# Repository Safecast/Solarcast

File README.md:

# Solarcast
Safecast Solarcast sensor device is designed to operate off-grid and sense environmental parameters. It consists of 5 key modules designed for maximal reuse.

## Modular design
 1. [Air sensor module](/air-module)
 2. [Geiger sensor module](/geiger-module)
 3. [Battery power module](/battery-module)
 4. [Communications module](/communications-module)
 5. [Gateway module](/gateway-module)

In an optimal design all modules have their own BLE processor and can be directly combined between each other, initial design is however only partially modular.

## Design parameters
The PCBs have to be designed in KiCad package.

---

#### License

Open data generated by Safecast is licensed under [CC0](https://creativecommons.org/publicdomain/zero/1.0/legalcode).

Hardware, Software, and Firmware licenses TBD.

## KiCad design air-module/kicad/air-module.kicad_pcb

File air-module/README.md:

# Air module for Solarcast
Air module is a standalone sensor unit that is a part of the Solarcast assembly and houses two particle sensors and a temperature and humidity sensor along with an optional BLE processor module.

## Design specification
* BLE module NRF [nRF52832 ANT](https://www.tindie.com/products/hnhoan/nrf52832-ant-bluetooth-le-arm-cortex-m4f-30-io/)
* Particle sensor [Alphasense OPC-N2](http://www.alphasense.com/index.php/products/optical-particle-counter/) (SPI)
* Particle sensor [PM2.5 PMS 5003](http://www.plantower.com/en/content/?108.html) (UART)
* Temperature and humidity sensor BME280 sensor (I2C SDO high 0x77)
* 5V power supply via USB connector (no USB data)
* Outdoor enclosure [PNR-2603](http://eu.mouser.com/ProductDetail/Bud-Industries/PNR-2603/?qs=sGAEpiMZZMsrGrAVj6eTvTO11XxqWC53gJbMy7TDIp4%3d)
* Dual channel high side Switch high-side switch [TPS2034D](http://www.ti.com/product/TPS2034D?keyMatch=TPS2034D&tisearch=Search-EN-Everything) each output for one AIR sensor, with bypass header jumpers.

## Extended details
* Waterproof [USB connector](http://eu.mouser.com/ProductDetail/Conxall-Switchcraft/DCP-USBCB-SC/?qs=sGAEpiMZZMulM8LPOQ%252byk0tOUVtDtVQ0KVOITCuLB%252bPJPE9H7T7ELA%3d%3d
) (data lines carry SWDIO & SWCLK signals)
* Internal 3V3 regulator
* Expansion connector 2x6 (IDC connector) with SPI, I2C and UART

## Connection details
The devices have the following connection details:

* Alphasense (leftmost wire on connector with wire crimp contacts facing up going away from you) Connector: Molex 'Pico Clasp' 6 way Housing, Part Number 501330-0600
 1. 5V
 2. SPI-SCLK
 3. SPI-MISO
 4. SPI-MOSI
 5. SPI-CS
 6. GND

* Plantower, no connector, solder wires
  1. 5V
  2. GND
  3. N/C
  4. RX (optional SCL) (add 0 ohm resistors to select between uart and i2c pins)
  5. TX (optional SDA) (add 0 ohm resistors to select between uart and i2c pins)
  6. N/C
  7. comm config (add solder jumpers for pull up/down)
  8. comm config (add solder jumpers for pull up/down)

*  nRF52832 module
 * Pin 3: P0.23	LED-RED
 * Pin 5: P0.25	TWI-SDA
 * Pin 6: P0.26 TWI-SCL
 * Pin 7: P0.27 UMUX-INH
 * Pin 18: 3.3V
 * Pin 19: GND
 * Pin 20: P0.07 TX
 * Pin 21: SWCLK/TCK
 * Pin 22: SWDIO/TMS
 * Pin 23: P0.08 RX
 * Pin 28: P0.03 SPI-MOSI
 * Pin 29: P0.04 SPI-MISO
 * Pin 30: P0.05 SPI-CS
 * Pin 31: P0.06 SPI-SCLK

 ## Board layout
 The PCB board has a connector of each particle sensor, BLE module on the short board edge and the USB connector on the edge between two rounded corners.

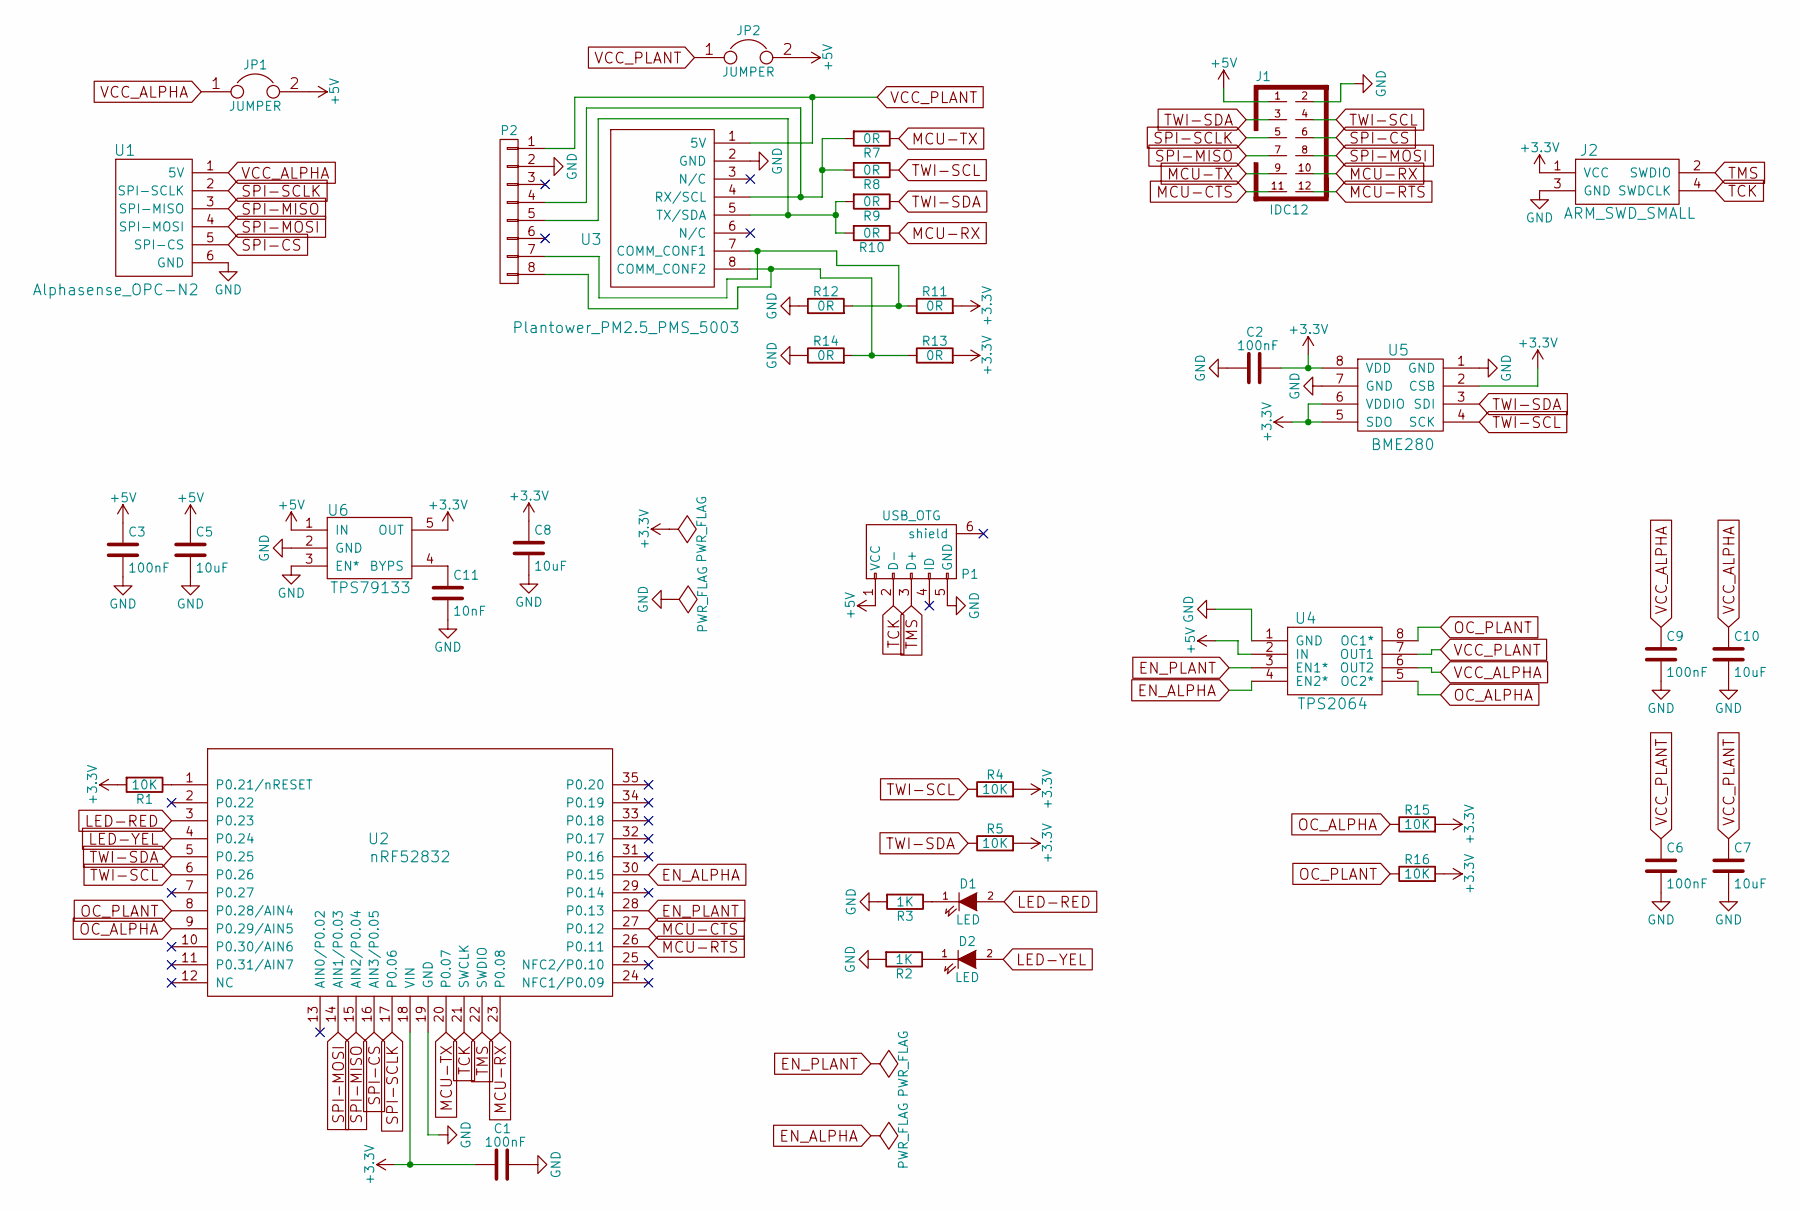
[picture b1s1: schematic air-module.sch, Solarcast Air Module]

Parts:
C1, C2, C3, C6, C9: 100nF; 0603_HandSoldering
C5, C7, C8, C10: 10uF; 0805_HandSoldering
C11: 10nF; 0603_HandSoldering
D1, D2: LED; LED_0603_HandSoldering
J1: IDC12; IDC12_connector
J2: ARM_SWD_SMALL; Socket_Strip_Straight_2x02
JP1, JP2: JUMPER; Socket_Strip_Straight_1x02
P1: USB_OTG; DCP-USBCB-SC
P2: CONN_01X08; Molex-53047-0810
R1, R4, R5, R15, R16: 10K; 0603_HandSoldering
R2, R3: 1K; 0603_HandSoldering
R7, R8, R9, R10, R11, R12, R13, R14: 0R; 0603_HandSoldering
U1: Alphasense_OPC-N2; Molex_501331-0607
U2: nRF52832; nRF52832-SMD
U3: Plantower_PM2.5_PMS_5003; Socket_Strip_Straight_1x08
U4: TPS2064
U5: BME280
U6: TPS79133

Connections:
+3V3: C1.2, C2.1, C8.1, J2.1 (VCC), R1.2, R4.2, R5.2, R11.2, R13.2, R15.2, R16.2, U2.18 (VIN), U5.2 (CSB), U5.5 (SDO), U5.6 (VDDIO), U5.8 (VDD), U6.5 (OUT)
+5V: C3.1, C5.1, J1.1, JP1.2, JP2.2, P1.1 (VCC), U4.2 (IN), U6.1 (IN)
EN_ALPHA: U2.30 (P0.15), U4.4 (EN2*)
EN_PLANT: U2.28 (P0.13), U4.3 (EN1*)
GND: C1.1, C2.2, C3.2, C5.2, C6.2, C7.2, C8.2, C9.2, C10.2, C11.2, J1.2, J2.3 (GND), P1.5 (GND), P2.2, R2.2, R3.2, R12.1, R14.1, U1.6 (GND), U2.19 (GND), U3.2 (GND), U4.1 (GND), U5.1 (GND), U5.7 (GND), U6.2 (GND), U6.3 (EN*)
LED-RED: D1.2 (A), U2.3 (P0.23)
LED-YEL: D2.2 (A), U2.4 (P0.24)
MCU-CTS: J1.11, U2.27 (P0.12)
MCU-RTS: J1.12, U2.26 (P0.11)
MCU-RX: J1.10, R10.1, U2.23 (P0.08)
MCU-TX: J1.9, R7.1, U2.20 (P0.07)
unnamed: C11.1, U6.4 (BYPS)
unnamed: D1.1 (K), R3.1
unnamed: D2.1 (K), R2.1
unnamed: P2.4, R7.2, R8.2, U3.4 (RX/SCL)
unnamed: P2.5, R9.2, R10.2, U3.5 (TX/SDA)
unnamed: P2.7, R11.1, R12.2, U3.7 (COMM_CONF1)
unnamed: P2.8, R13.1, R14.2, U3.8 (COMM_CONF2)
unnamed: R1.1, U2.1 (P0.21/nRESET)
OC_ALPHA: R15.1, U2.9 (P0.29/AIN5), U4.5 (OC2*)
OC_PLANT: R16.1, U2.8 (P0.28/AIN4), U4.8 (OC1*)
SPI-CS: J1.6, U1.5 (SPI-CS), U2.16 (AIN3/P0.05)
SPI-MISO: J1.7, U1.3 (SPI-MISO), U2.15 (AIN2/P0.04)
SPI-MOSI: J1.8, U1.4 (SPI-MOSI), U2.14 (AIN1/P0.03)
SPI-SCLK: J1.5, U1.2 (SPI-SCLK), U2.17 (P0.06)
TCK: J2.4 (SWDCLK), P1.2 (D-), U2.21 (SWCLK)
TMS: J2.2 (SWDIO), P1.3 (D+), U2.22 (SWDIO)
TWI-SCL: J1.4, R4.1, R8.1, U2.6 (P0.26), U5.4 (SCK)
TWI-SDA: J1.3, R5.1, R9.1, U2.5 (P0.25), U5.3 (SDI)
VCC_ALPHA: C9.1, C10.1, JP1.1, U1.1 (5V), U4.6 (OUT2)
VCC_PLANT: C6.1, C7.1, JP2.1, P2.1, U3.1 (5V), U4.7 (OUT1)

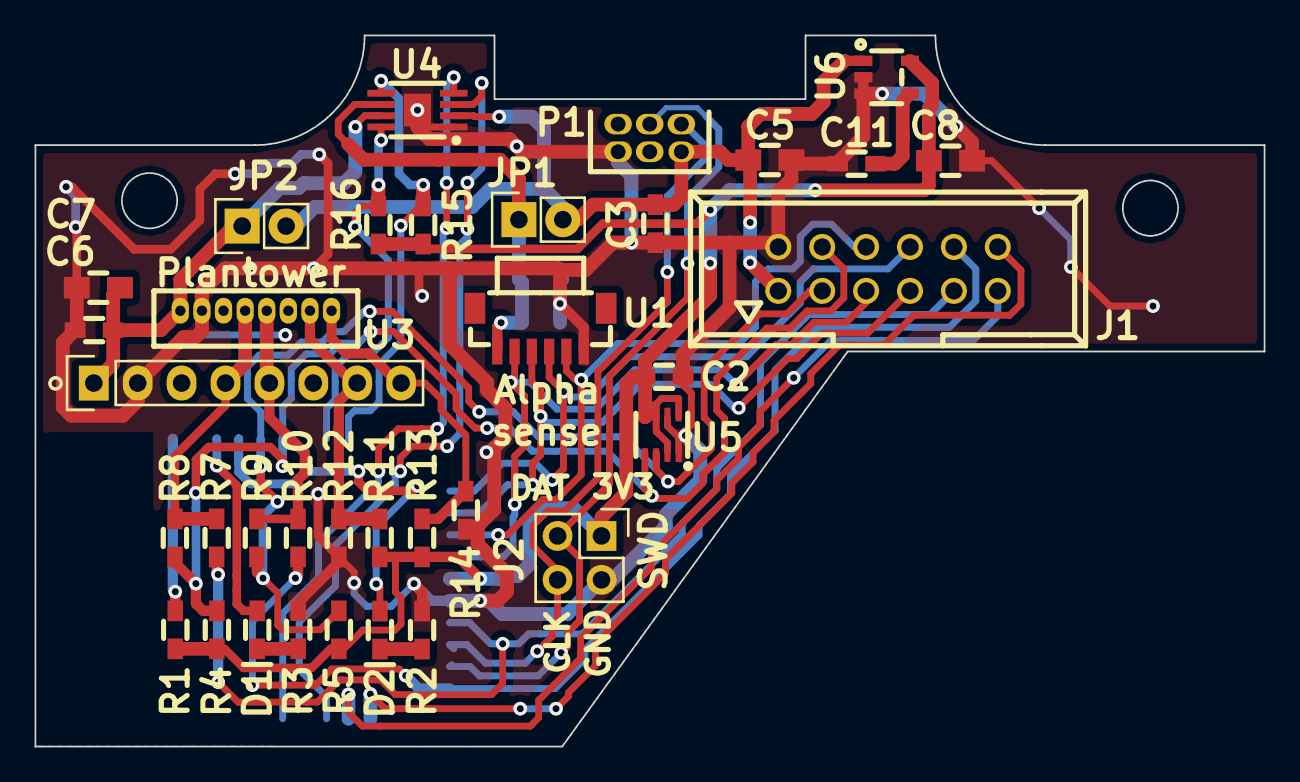
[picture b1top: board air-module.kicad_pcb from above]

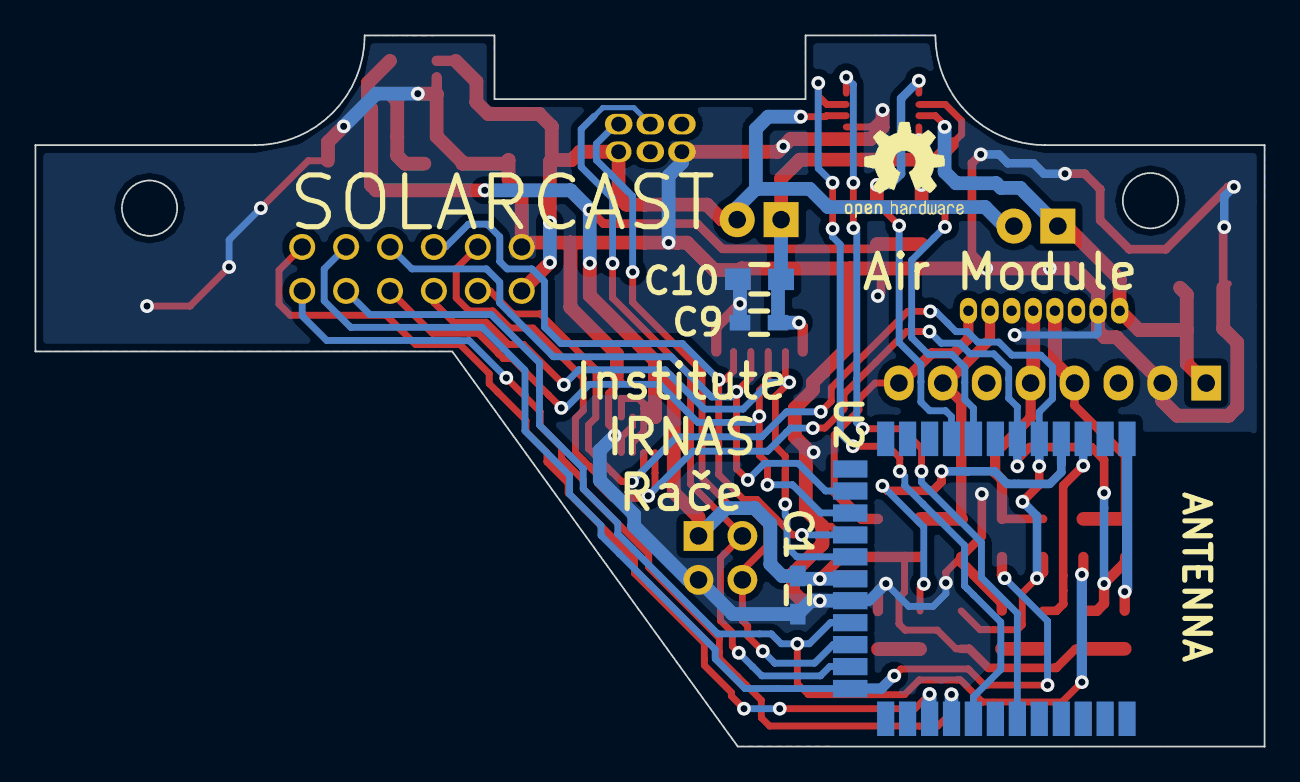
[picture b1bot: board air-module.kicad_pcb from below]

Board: 2 copper layers, 71.1 x 41.1 mm, 39 parts (4 on the bottom side), 31 nets.

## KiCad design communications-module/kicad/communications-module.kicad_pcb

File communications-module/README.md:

# Communications module for Solarcast
Communications module operates as the main module for the complete Solarcast assembly and is primarily a BLE device with other comms modules being plugged in.

## Design specification
* NRF module [nRF52832 ANT](https://www.tindie.com/products/hnhoan/nrf52832-ant-bluetooth-le-arm-cortex-m4f-30-io/)
* Programmer [CMSIS-DAP](https://www.tindie.com/products/hnhoan/cmsis-dap-arm-debug-jtagswd-module-drag-and-drop/)
* [GPS module](https://www.adafruit.com/products/790)
* [Adafruit FONA 3G module](https://www.adafruit.com/products/2691) (Note version difference between USA and EU)
* GSM antenna [FXUB66.07.0150C](http://www.mouser.com/ProductDetail/Taoglas/FXUB66070150C/?qs=L8NdhHdZHXxzH3hw8Na69A%3D%3D)
* LORA antenna [FXUB66.01.0150C](http://www.mouser.com/ProductDetail/Taoglas/FXUB66010150C/?qs=sGAEpiMZZMuBTKBKvsBmlEt2wojY8dgW39nSVW3ZfN0%3d)
* BME280 sensor (SDO low 0x76)
* Add accelerometer [LIS3DSH](https://www.adafruit.com/products/2809) footprint for the ic and pins for breakout
* UART MUX SN74LV4052AD SOIC-16
* USB connector to outside world http://eu.mouser.com/ProductDetail/Conxall-Switchcraft/DCP-USBCB-SC/?qs=sGAEpiMZZMulM8LPOQ%252byk0tOUVtDtVQ0KVOITCuLB%252bPJPE9H7T7ELA%3d%3d
* Case: PN-1335
* Add a GPIO expansion port for later work (UART for Air can be on it and I2C and SPI)
* Three internal USB connectors, not carrying USB data
 * USB0 - data pins select between I2C and programming pins
 * USB1 - data pins select between I2C and programming pins
 * USB2 - data pins select between GEIGER0/GEIGER1 and programming pins
* Connector for power module
* 2 groove expansion ports
* External power switch mounted on the box.

## Power supply configuration
Solar operation of the device and minimal power consumption in the standby state govern the design requirements.

Power flow: Solar cell-> Power module (built-in regulators) -> Comms module -> Power switch and fan out to:
* Switch high-side 5V - USB0 for Air module - ENABLE-AIR - 250mA peak - [TPS2034D](http://www.ti.com/product/TPS2034D?keyMatch=TPS2034D&tisearch=Search-EN-Everything) regulated from battery pack
* Switch high-side 5V - USB1 for Geiger module - ENABLE-GEIG - 50mA peak - [TPS2034D](http://www.ti.com/product/TPS2034D?keyMatch=TPS2034D&tisearch=Search-EN-Everything) regulated from battery pack
* Switch high-side 5V - USB2 -reserve- 1A peak [TPS2034D](http://www.ti.com/product/TPS2034D?keyMatch=TPS2034D&tisearch=Search-EN-Everything)
* Switch high-side 5V - backup - 1A peak [TPS2034D](http://www.ti.com/product/TPS2034D?keyMatch=TPS2034D&tisearch=Search-EN-Everything)

Power switch disconnects power between power module and comms module.

Add headers for mosfet bypass for current consumption measurement and jumpers prior to voltage regulators.

## Board layout
The board is designed as a main board with all other modules connecting to it.

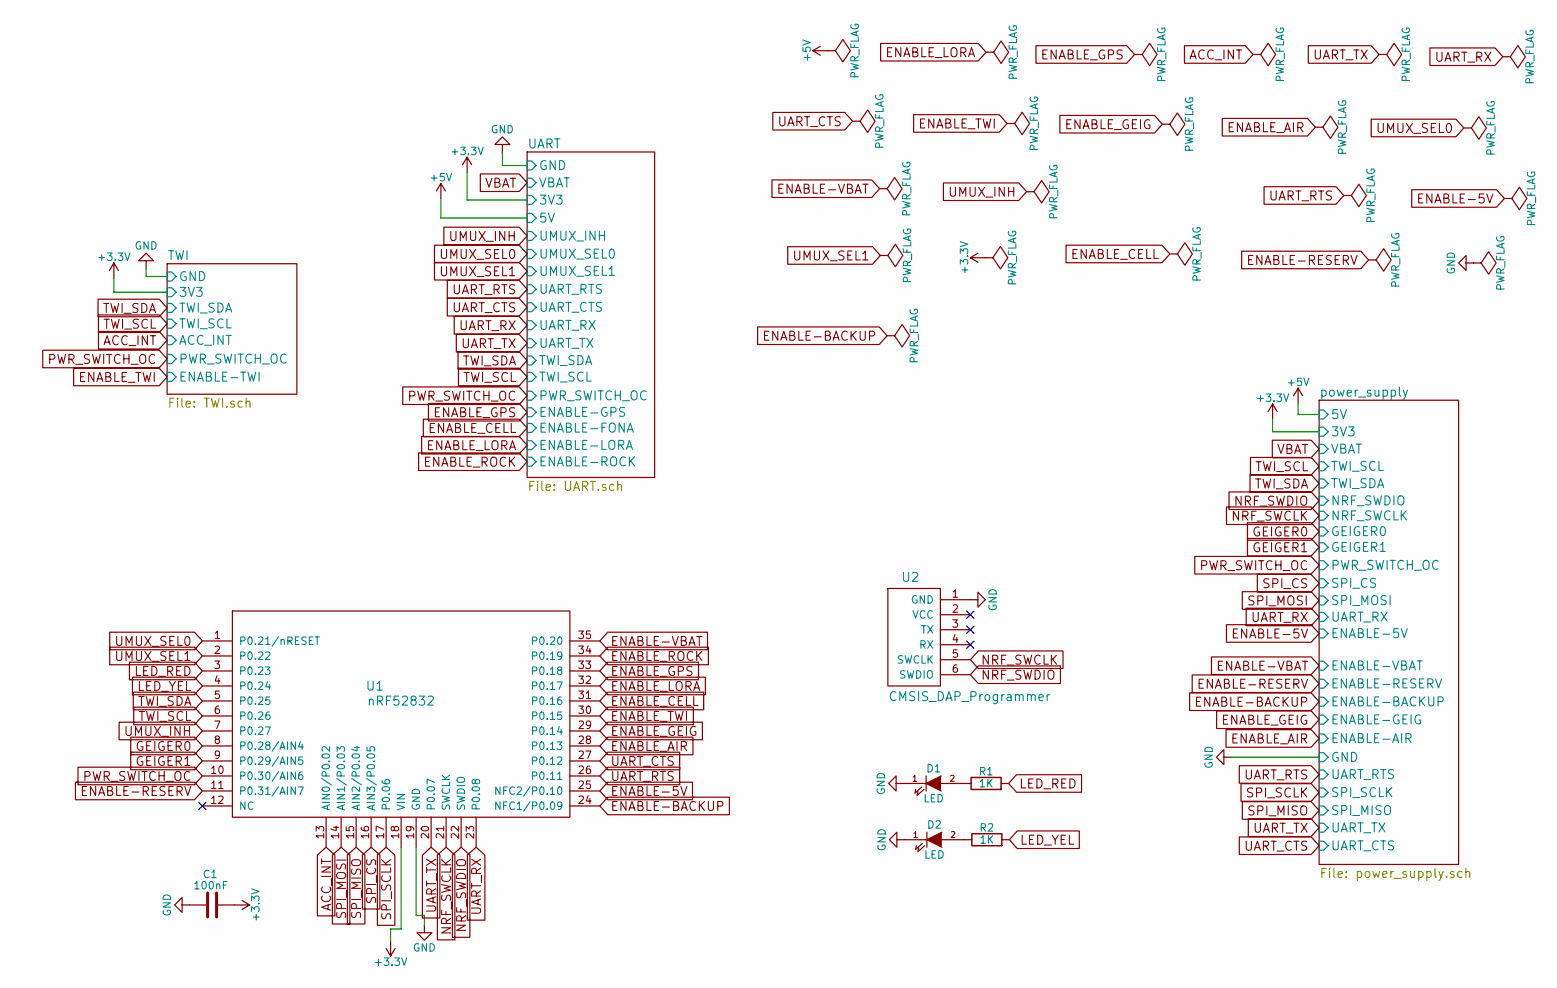
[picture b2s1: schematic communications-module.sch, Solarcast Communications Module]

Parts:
C1: 100nF; 0603_HandSoldering
D1, D2: LED; LED_0603_HandSoldering
R1, R2: 1K; 0603_HandSoldering
U1: nRF52832; nRF52832-SMD
U2: CMSIS_DAP_Programmer; CMSIS_DAP_Breakout

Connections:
+3V3: C1.2, U1.18 (VIN); also elsewhere on the board
ACC_INT: U1.13 (AIN0/P0.02); also elsewhere on the board
ENABLE-5V: U1.25 (NFC2/P0.10); also elsewhere on the board
ENABLE-AIR: U1.28 (P0.13); also elsewhere on the board
ENABLE-BACKUP: U1.24 (NFC1/P0.09); also elsewhere on the board
ENABLE-FONA: U1.31 (P0.16); also elsewhere on the board
ENABLE-GEIG: U1.29 (P0.14); also elsewhere on the board
ENABLE-GPS: U1.33 (P0.18); also elsewhere on the board
ENABLE-LORA: U1.32 (P0.17); also elsewhere on the board
ENABLE-RESERV: U1.11 (P0.31/AIN7); also elsewhere on the board
ENABLE-ROCK: U1.34 (P0.19); also elsewhere on the board
ENABLE-TWI: U1.30 (P0.15); also elsewhere on the board
ENABLE-VBAT: U1.35 (P0.20); also elsewhere on the board
GEIGER0: U1.8 (P0.28/AIN4); also elsewhere on the board
GEIGER1: U1.9 (P0.29/AIN5); also elsewhere on the board
LED_RED: R1.2, U1.3 (P0.23)
LED_YEL: R2.2, U1.4 (P0.24)
NRF_SWCLK: U1.21 (SWCLK), U2.5 (SWCLK); also elsewhere on the board
NRF_SWDIO: U1.22 (SWDIO), U2.6 (SWDIO); also elsewhere on the board
unnamed: D1.2 (A), R1.1
unnamed: D2.2 (A), R2.1
PWR_SWITCH_OC: U1.10 (P0.30/AIN6); also elsewhere on the board
SPI_CS: U1.16 (AIN3/P0.05); also elsewhere on the board
SPI_MISO: U1.15 (AIN2/P0.04); also elsewhere on the board
SPI_MOSI: U1.14 (AIN1/P0.03); also elsewhere on the board
SPI_SCLK: U1.17 (P0.06); also elsewhere on the board
TWI_SCL: U1.6 (P0.26); also elsewhere on the board
TWI_SDA: U1.5 (P0.25); also elsewhere on the board
UART_CTS: U1.27 (P0.12); also elsewhere on the board
UART_RTS: U1.26 (P0.11); also elsewhere on the board
UART_RX: U1.23 (P0.08); also elsewhere on the board
UART_TX: U1.20 (P0.07); also elsewhere on the board
UMUX_INH: U1.7 (P0.27); also elsewhere on the board
UMUX_SEL0: U1.1 (P0.21/nRESET); also elsewhere on the board

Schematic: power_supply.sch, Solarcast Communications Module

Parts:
J1: IDC12; IDC12_connector
JP1, JP2, JP5, JP6, JP7, JP8: JUMPER3; Socket_Strip_Straight_1x03_Pitch2.54mm
JP3, JP4, JP11, JP12: Jumper_NC_Small; Socket_Strip_Straight_1x02_Pitch2.54mm
P2, P3, P4: USB_A; USB_A_receptacle
P5: BACKUP; Socket_Strip_Straight_1x02_Pitch2.54mm
R3: 10K; 0603_HandSoldering
U3, U5: TPS2064
U4: PWR_CONN; IDC10_connector

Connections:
+3V3: R3.1, U4.5 (3V3); also elsewhere on the board
+5V: JP3.1, JP4.1, JP11.1, JP12.1, U3.2 (IN), U4.3 (5V), U5.2 (IN); also elsewhere on the board
AIR_5V: J1.1, JP11.2, P3.1 (VCC), U5.6 (OUT2)
BACKUP_5V: JP4.2, P5.1, U3.6 (OUT2)
ENABLE-5V: U4.4 (EN_5V); also elsewhere on the board
ENABLE-AIR: U5.4 (EN2*); also elsewhere on the board
ENABLE-BACKUP: U3.4 (EN2*); also elsewhere on the board
ENABLE-GEIG: U5.3 (EN1*); also elsewhere on the board
ENABLE-RESERV: U3.3 (EN1*); also elsewhere on the board
ENABLE-VBAT: U4.8 (EN_VBAT); also elsewhere on the board
GEIGER0: JP1.1; also elsewhere on the board
GEIGER1: JP2.3; also elsewhere on the board
GEIGER_5V: JP12.2, P2.1 (VCC), U5.7 (OUT1)
NRF_SWCLK: JP1.3, JP5.3, JP7.3; also elsewhere on the board
NRF_SWDIO: JP2.1, JP6.1, JP8.1; also elsewhere on the board
unnamed: JP1.2, P2.2 (D-)
unnamed: JP2.2, P2.3 (D+)
unnamed: JP5.2, P3.2 (D-)
unnamed: JP6.2, P3.3 (D+)
unnamed: JP7.2, P4.2 (D-)
unnamed: JP8.2, P4.3 (D+)
PWR_SWITCH_OC: R3.2, U3.5 (OC2*), U3.8 (OC1*), U5.5 (OC2*), U5.8 (OC1*); also elsewhere on the board
RESERV_5V: JP3.2, P4.1 (VCC), U3.7 (OUT1)
SPI_CS: J1.6; also elsewhere on the board
SPI_MISO: J1.7; also elsewhere on the board
SPI_MOSI: J1.8; also elsewhere on the board
SPI_SCLK: J1.5; also elsewhere on the board
TWI_SCL: J1.4, JP5.1, JP7.1, U4.1 (I2C_SCL); also elsewhere on the board
TWI_SDA: J1.3, JP6.3, JP8.3, U4.2 (I2C_SDA); also elsewhere on the board
UART_CTS: J1.11; also elsewhere on the board
UART_RTS: J1.12; also elsewhere on the board
UART_RX: J1.10; also elsewhere on the board
UART_TX: J1.9; also elsewhere on the board
VBAT: U4.7 (VBAT); also elsewhere on the board

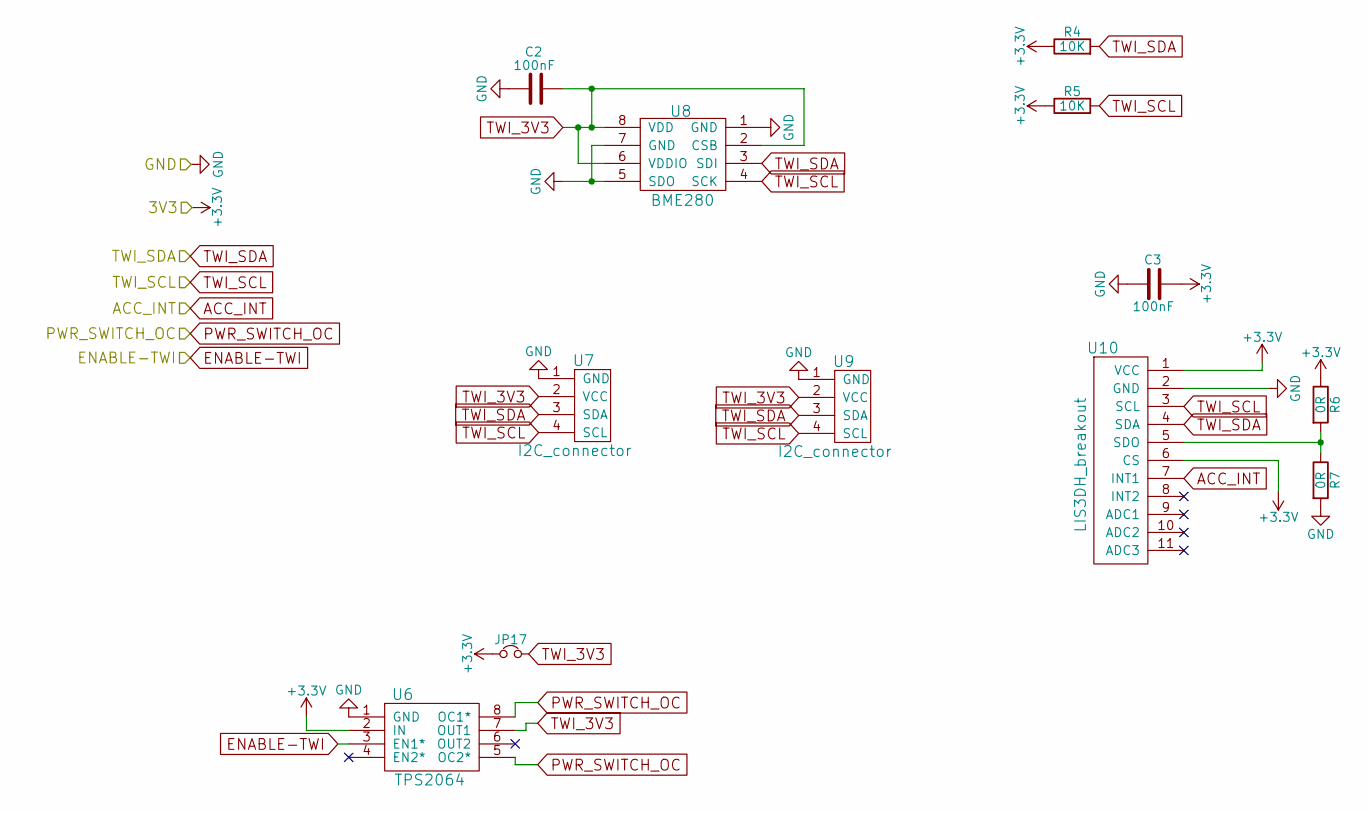
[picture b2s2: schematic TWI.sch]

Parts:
C2, C3: 100nF; 0603_HandSoldering
JP17: Jumper_NC_Small; Socket_Strip_Straight_1x02_Pitch2.54mm
R4, R5: 10K; 0603_HandSoldering
R6, R7: 0R; 0603_HandSoldering
U6: TPS2064
U7, U9: I2C_connector; DIP_Grove_4P-2_0
U8: BME280
U10: LIS3DH_breakout; LIS3DH_breakout_vertical

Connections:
+3V3: C3.2, JP17.1, R4.1, R5.1, R6.1, U6.2 (IN), U10.1 (VCC), U10.6 (CS); also elsewhere on the board
ACC_INT: U10.7 (INT1); also elsewhere on the board
ENABLE-TWI: U6.3 (EN1*); also elsewhere on the board
unnamed: R6.2, R7.1, U10.5 (SDO)
PWR_SWITCH_OC: U6.5 (OC2*), U6.8 (OC1*); also elsewhere on the board
TWI_3V3: C2.2, JP17.2, U6.7 (OUT1), U7.2 (VCC), U8.2 (CSB), U8.6 (VDDIO), U8.8 (VDD), U9.2 (VCC)
TWI_SCL: R5.2, U7.4 (SCL), U8.4 (SCK), U9.4 (SCL), U10.3 (SCL); also elsewhere on the board
TWI_SDA: R4.2, U7.3 (SDA), U8.3 (SDI), U9.3 (SDA), U10.4 (SDA); also elsewhere on the board

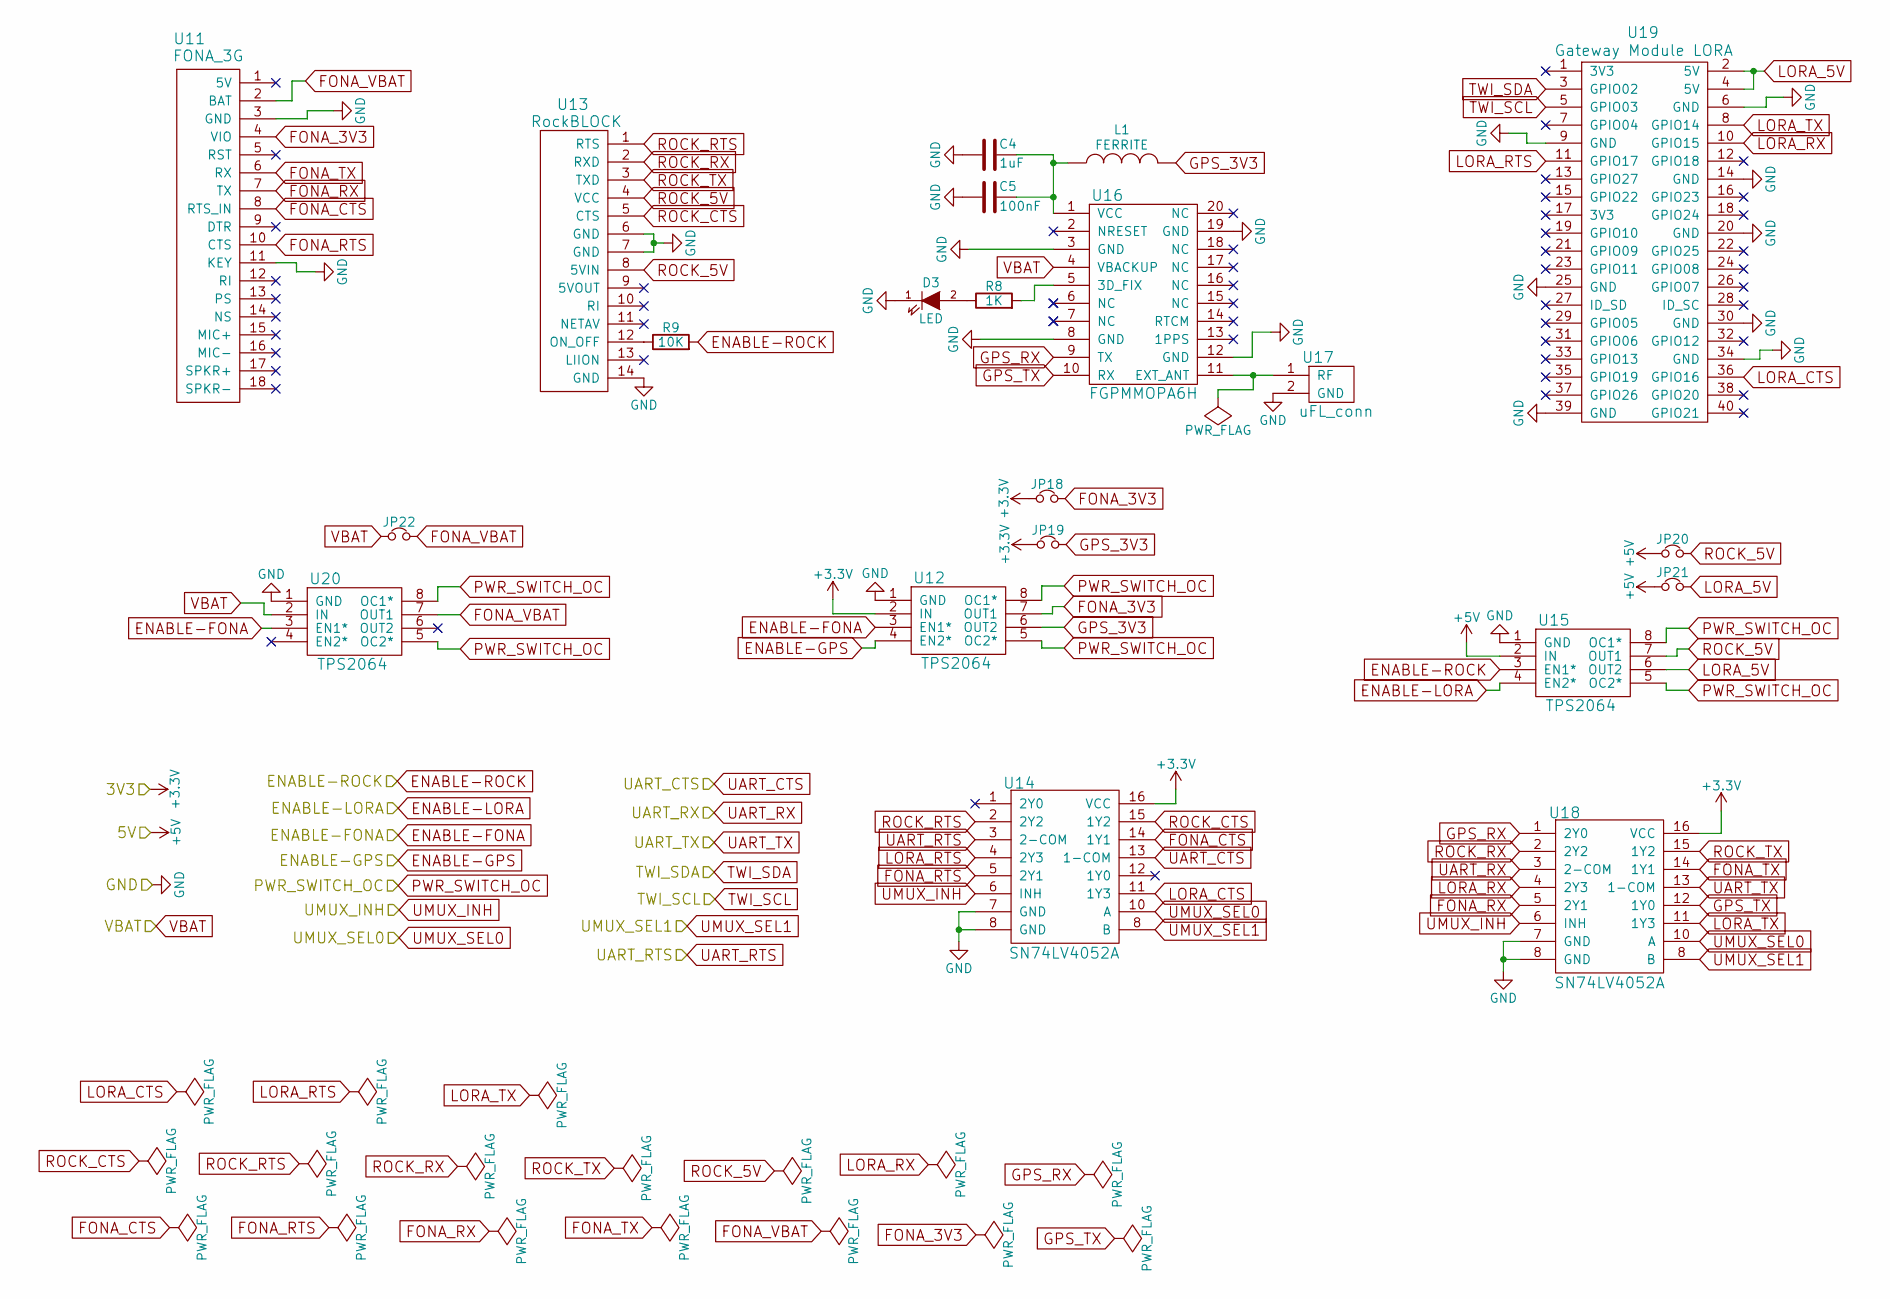
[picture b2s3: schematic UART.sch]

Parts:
C4: 1uF; 0603_HandSoldering
C5: 100nF; 0603_HandSoldering
D3: LED; LED_0603_HandSoldering
JP18, JP19, JP20, JP21, JP22: Jumper_NC_Small; Socket_Strip_Straight_1x02_Pitch2.54mm
L1: FERRITE; 0603_HandSoldering
R8: 1K; 0603_HandSoldering
R9: 10K; 0603_HandSoldering
U11: FONA_3G; FONA_3G_vertical
U12, U15, U20: TPS2064
U13: RockBLOCK; RockBlock_vertical
U14, U18: SN74LV4052A
U16: FGPMMOPA6H; FGPMMOPA6H_GPS
U17: uFL_conn; U.FL-R-SMT
U19: Gateway Module LORA; Solarcast_Gateway_Module

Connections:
+3V3: JP18.1, JP19.1, U12.2 (IN), U14.16 (VCC), U18.16 (VCC); also elsewhere on the board
+5V: JP20.1, JP21.1, U15.2 (IN); also elsewhere on the board
ENABLE-FONA: U12.3 (EN1*), U20.3 (EN1*); also elsewhere on the board
ENABLE-GPS: U12.4 (EN2*); also elsewhere on the board
ENABLE-LORA: U15.4 (EN2*); also elsewhere on the board
ENABLE-ROCK: R9.2, U15.3 (EN1*); also elsewhere on the board
FONA_3V3: JP18.2, U11.4 (VIO), U12.7 (OUT1)
FONA_CTS: U11.8 (RTS_IN), U14.14 (1Y1)
FONA_RTS: U11.10 (CTS), U14.5 (2Y1)
FONA_RX: U11.7 (TX), U18.5 (2Y1)
FONA_TX: U11.6 (RX), U18.14 (1Y1)
FONA_VBAT: JP22.2, U11.2 (BAT), U20.7 (OUT1)
GPS_3V3: JP19.2, L1.2, U12.6 (OUT2)
GPS_RX: U16.9 (TX), U18.1 (2Y0)
GPS_TX: U16.10 (RX), U18.12 (1Y0)
LORA_5V: JP21.2, U15.6 (OUT2), U19.2 (5V), U19.4 (5V)
LORA_CTS: U14.11 (1Y3), U19.36 (GPIO16)
LORA_RTS: U14.4 (2Y3), U19.11 (GPIO17)
LORA_RX: U18.4 (2Y3), U19.10 (GPIO15)
LORA_TX: U18.11 (1Y3), U19.8 (GPIO14)
unnamed: C4.2, C5.2, L1.1, U16.1 (VCC)
unnamed: D3.2 (A), R8.1
unnamed: R8.2, U16.5 (3D_FIX)
unnamed: R9.1, U13.12 (ON_OFF)
unnamed: U16.11 (EXT_ANT), U17.1 (RF)
PWR_SWITCH_OC: U12.5 (OC2*), U12.8 (OC1*), U15.5 (OC2*), U15.8 (OC1*), U20.5 (OC2*), U20.8 (OC1*); also elsewhere on the board
ROCK_5V: JP20.2, U13.4 (VCC), U13.8 (5VIN), U15.7 (OUT1)
ROCK_CTS: U13.5 (CTS), U14.15 (1Y2)
ROCK_RTS: U13.1 (RTS), U14.2 (2Y2)
ROCK_RX: U13.2 (RXD), U18.2 (2Y2)
ROCK_TX: U13.3 (TXD), U18.15 (1Y2)
TWI_SCL: U19.5 (GPIO03); also elsewhere on the board
TWI_SDA: U19.3 (GPIO02); also elsewhere on the board
UART_CTS: U14.13 (1-COM); also elsewhere on the board
UART_RTS: U14.3 (2-COM); also elsewhere on the board
UART_RX: U18.3 (2-COM); also elsewhere on the board
UART_TX: U18.13 (1-COM); also elsewhere on the board
UMUX_INH: U14.6 (INH), U18.6 (INH); also elsewhere on the board
UMUX_SEL0: U14.10 (A), U18.10 (A); also elsewhere on the board
VBAT: JP22.1, U16.4 (VBACKUP), U20.2 (IN); also elsewhere on the board

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
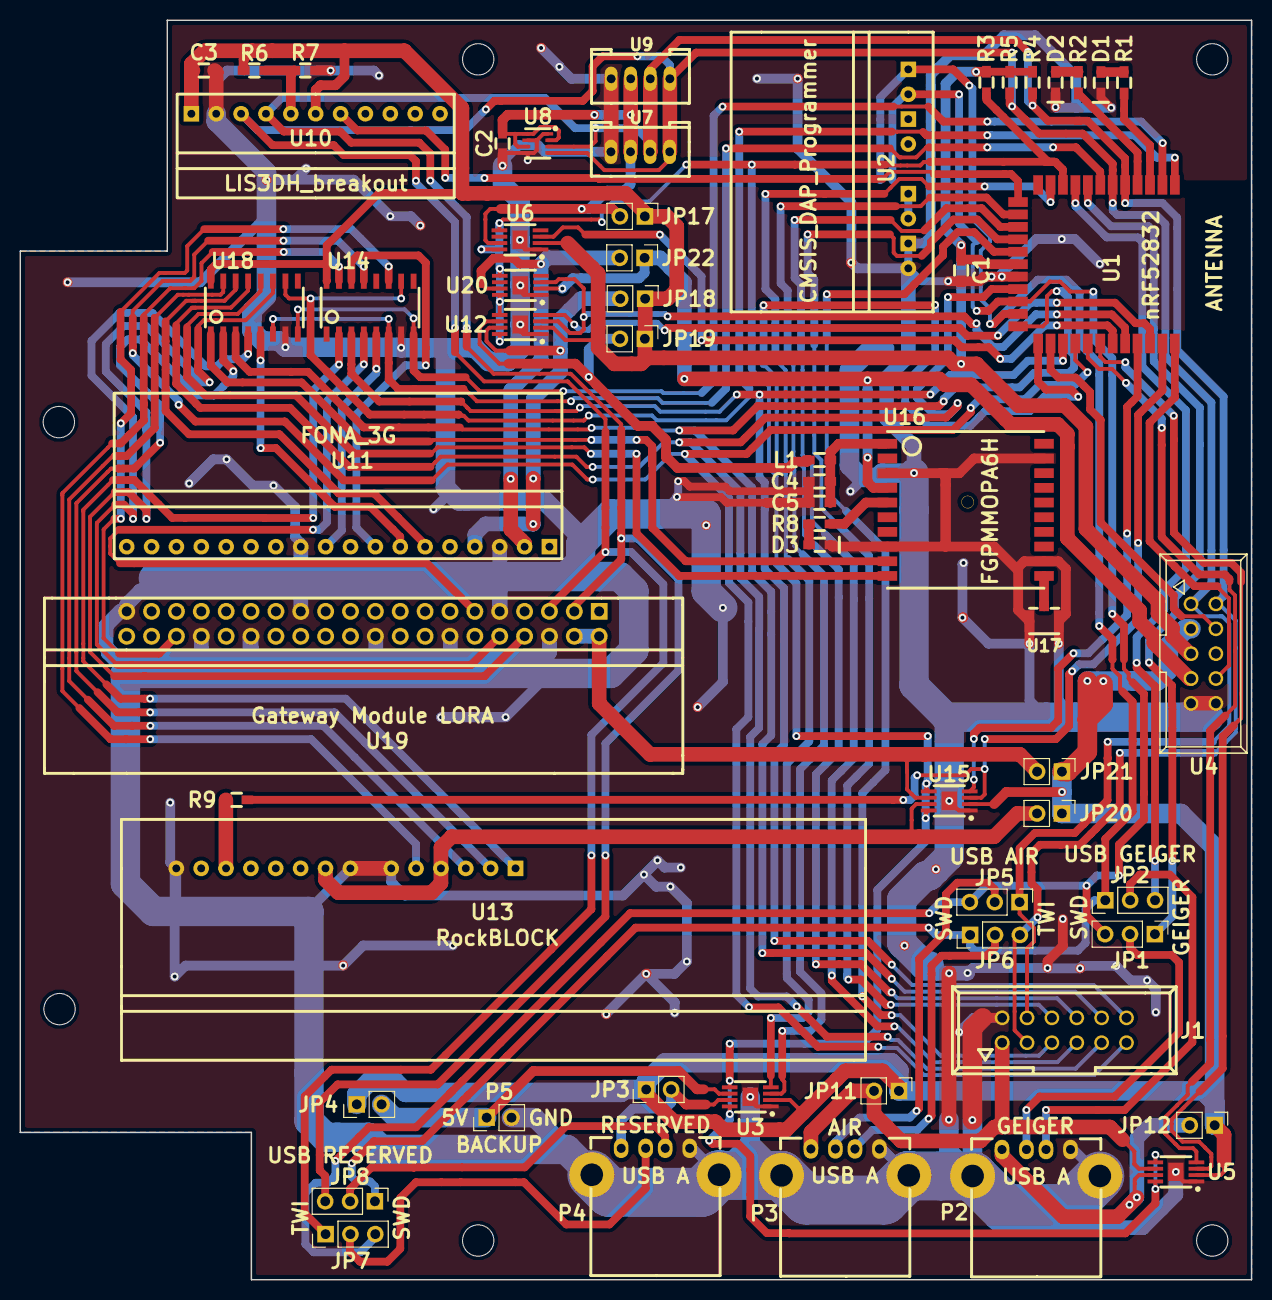
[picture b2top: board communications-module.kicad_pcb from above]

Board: 2 copper layers, 125.8 x 128.6 mm, 59 parts (0 on the bottom side), 74 nets.

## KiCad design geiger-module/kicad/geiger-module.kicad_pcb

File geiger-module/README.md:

# Geiger module for Solarcast
Geiger module is a standalone sensor unit that is a part of the Solarcast assembly and houses two Geiger tubes and a temperature and humidity sensor along with an optional BLE processor module.

## Design specification
* BLE module NRF [nRF52832 ANT](https://www.tindie.com/products/hnhoan/nrf52832-ant-bluetooth-le-arm-cortex-m4f-30-io/)
* Geiger pancake sensor (may be a stack of two)
* Geiger gamma compensated tube sensor
* Temperature and humidity sensor BME280 sensor (I2C SDO high 0x77)
* 5V power supply via USB connector (no USB data)
* Outdoor enclosure [PNR-2603](http://eu.mouser.com/ProductDetail/Bud-Industries/PNR-2603/?qs=sGAEpiMZZMsrGrAVj6eTvTO11XxqWC53gJbMy7TDIp4%3d)
* BLE module LED-RED

## Extended details
* Waterproof [USB connector](http://eu.mouser.com/ProductDetail/Conxall-Switchcraft/DCP-USBCB-SC/?qs=sGAEpiMZZMulM8LPOQ%252byk0tOUVtDtVQ0KVOITCuLB%252bPJPE9H7T7ELA%3d%3d
) (data lines carry SWDIO & SWCLK signals or Geiger 1 and Geiger 2 output signals, configuration depending via jumper)
* Internal 3V3 regulator
* 2pcs iRover HV board, stacked

## Connection details
The devices have the following connection details:

*  nRF52832 module
 * Pin 3: P0.23	LED-RED
 * Pin 5: P0.25	TWI-SDA
 * Pin 6: P0.26 TWI-SCL
 * Pin 7: P0.28	GEIGER0
 * Pin 8: P0.29 GEIGER1
 * Pin 18: 3.3V
 * Pin 19: GND
 * Pin 21: SWCLK/TCK
 * Pin 22: SWDIO/TMS

## Board layout
The PCB board has the two tubes mounted on one side with cables passing though and being connected directly to iRover boards on the other side. These boards are placed one next to the other. BLE module is placed somewhere along the edge, USB connector is on the short edge opposite to the side where the cutout for cables is.

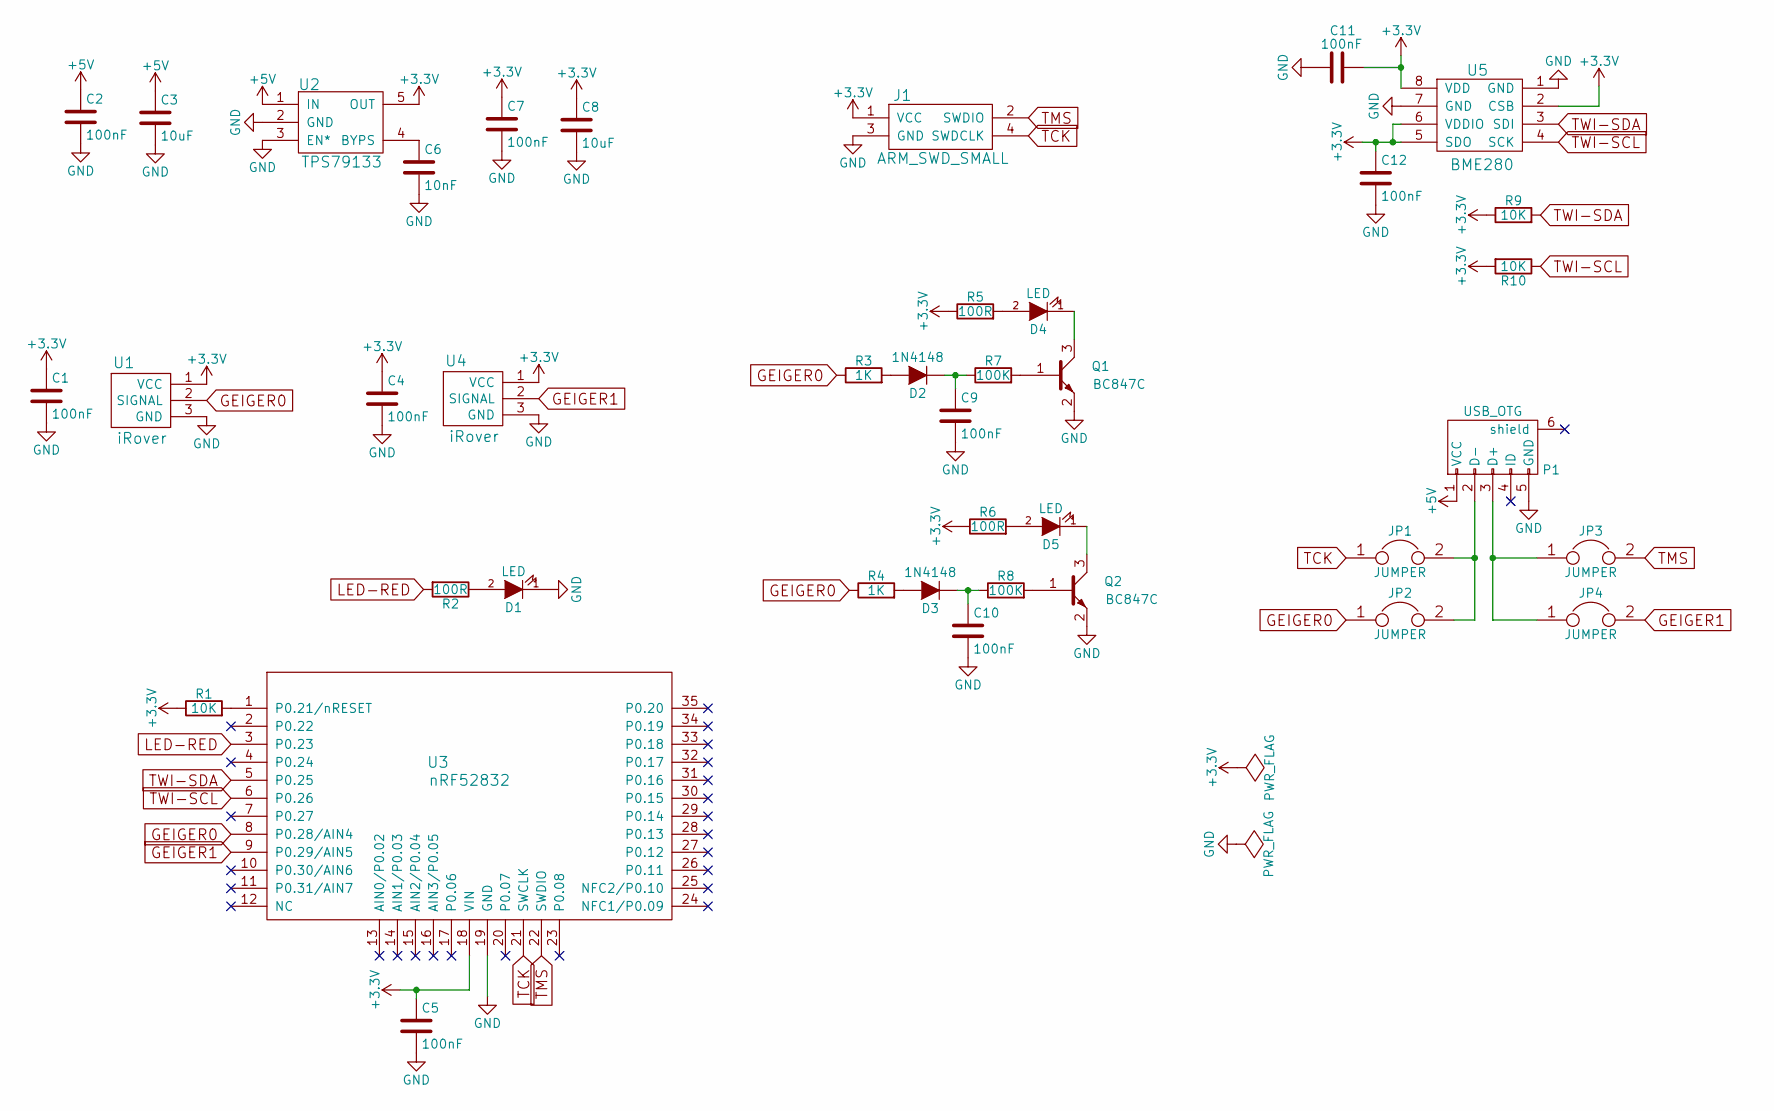
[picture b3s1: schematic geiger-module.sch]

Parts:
C1, C2, C4, C5, C7, C9, C10, C11, C12: 100nF; 0603_HandSoldering
C3, C8: 10uF; 0603_HandSoldering
C6: 10nF; 0603_HandSoldering
D1, D4, D5: LED; LED_0603_HandSoldering
D2, D3: 1N4148; SOD-323
J1: ARM_SWD_SMALL; Socket_Strip_Straight_2x02
JP1, JP2, JP3, JP4: JUMPER; Socket_Strip_Straight_1x02
P1: USB_OTG; DCP-USBCB-SC
Q1, Q2: BC847C; SOT-23
R1, R9, R10: 10K; 0603_HandSoldering
R2, R5, R6: 100R; 0603_HandSoldering
R3, R4: 1K; 0603_HandSoldering
R7, R8: 100K; 0603_HandSoldering
U1, U4: iRover; B3B-PH-SM4-TB_IROVER_CONNECTOR
U2: TPS79133
U3: nRF52832; nRF52832-SMD
U5: BME280

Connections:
+3V3: C1.1, C4.1, C5.1, C7.1, C8.1, C11.1, C12.1, J1.1 (VCC), R1.1, R5.1, R6.1, R9.1, R10.2, U1.1 (VCC), U2.5 (OUT), U3.18 (VIN), U4.1 (VCC), U5.2 (CSB), U5.5 (SDO), U5.6 (VDDIO), U5.8 (VDD)
+5V: C2.1, C3.1, P1.1 (VCC), U2.1 (IN)
GEIGER0: JP2.1, R3.1, R4.1, U1.2 (SIGNAL), U3.8 (P0.28/AIN4)
GEIGER1: JP4.2, U3.9 (P0.29/AIN5), U4.2 (SIGNAL)
GND: C1.2, C2.2, C3.2, C4.2, C5.2, C6.2, C7.2, C8.2, C9.2, C10.2, C11.2, C12.2, D1.1 (K), J1.3 (GND), P1.5 (GND), Q1.2 (E), Q2.2 (E), U1.3 (GND), U2.2 (GND), U2.3 (EN*), U3.19 (GND), U4.3 (GND), U5.1 (GND), U5.7 (GND)
LED-RED: R2.2, U3.3 (P0.23)
unnamed: C6.1, U2.4 (BYPS)
unnamed: C9.1, D2.1 (K), R7.1
unnamed: C10.1, D3.1 (K), R8.1
unnamed: D1.2 (A), R2.1
unnamed: D2.2 (A), R3.2
unnamed: D3.2 (A), R4.2
unnamed: D4.1 (K), Q1.3 (C)
unnamed: D4.2 (A), R5.2
unnamed: D5.1 (K), Q2.3 (C)
unnamed: D5.2 (A), R6.2
unnamed: JP1.2, JP2.2, P1.2 (D-)
unnamed: JP3.1, JP4.1, P1.3 (D+)
unnamed: Q1.1 (B), R7.2
unnamed: Q2.1 (B), R8.2
unnamed: R1.2, U3.1 (P0.21/nRESET)
TCK: J1.4 (SWDCLK), JP1.1, U3.21 (SWCLK)
TMS: J1.2 (SWDIO), JP3.2, U3.22 (SWDIO)
TWI-SCL: R10.1, U3.6 (P0.26), U5.4 (SCK)
TWI-SDA: R9.2, U3.5 (P0.25), U5.3 (SDI)

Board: 2 copper layers, 40 parts (1 on the bottom side), 25 nets, no tracks yet.
